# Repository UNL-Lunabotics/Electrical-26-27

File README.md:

# Electrical-26-27
Electrical's pcb projects and documentation.

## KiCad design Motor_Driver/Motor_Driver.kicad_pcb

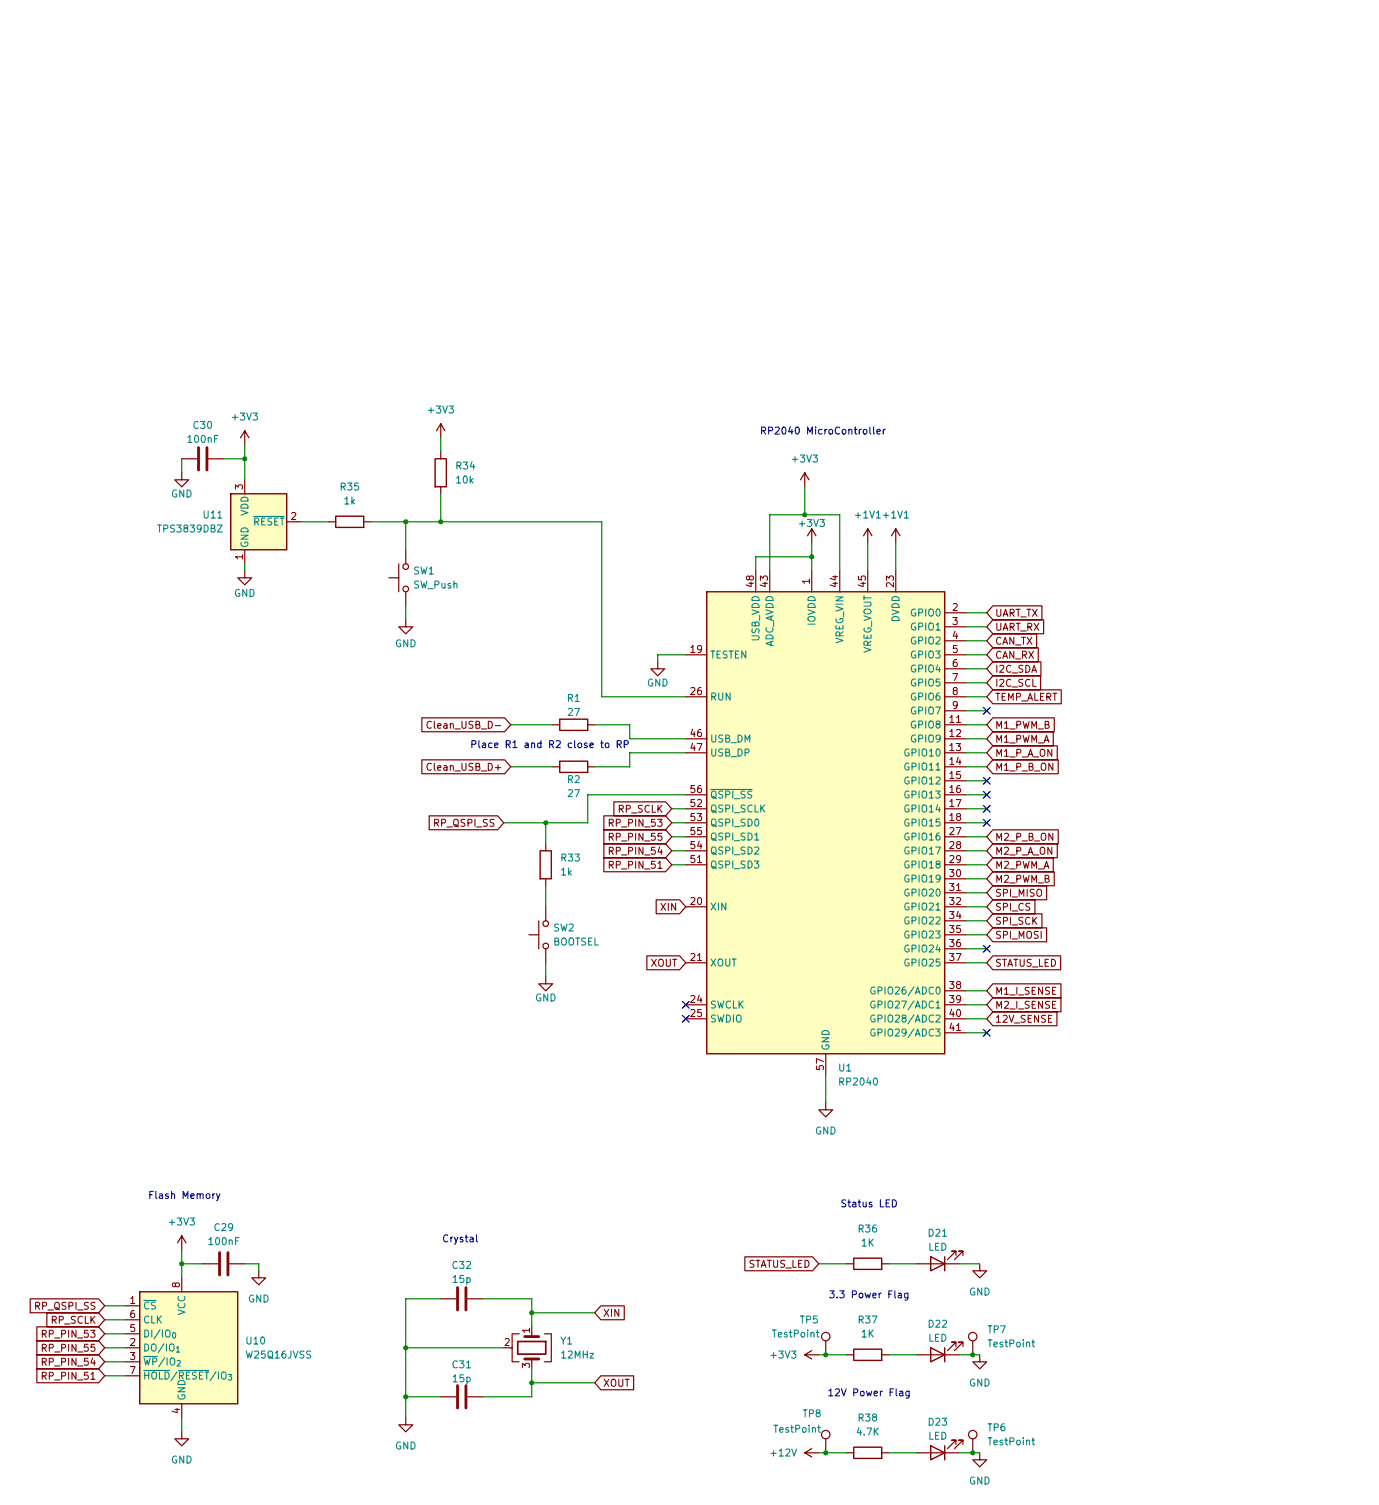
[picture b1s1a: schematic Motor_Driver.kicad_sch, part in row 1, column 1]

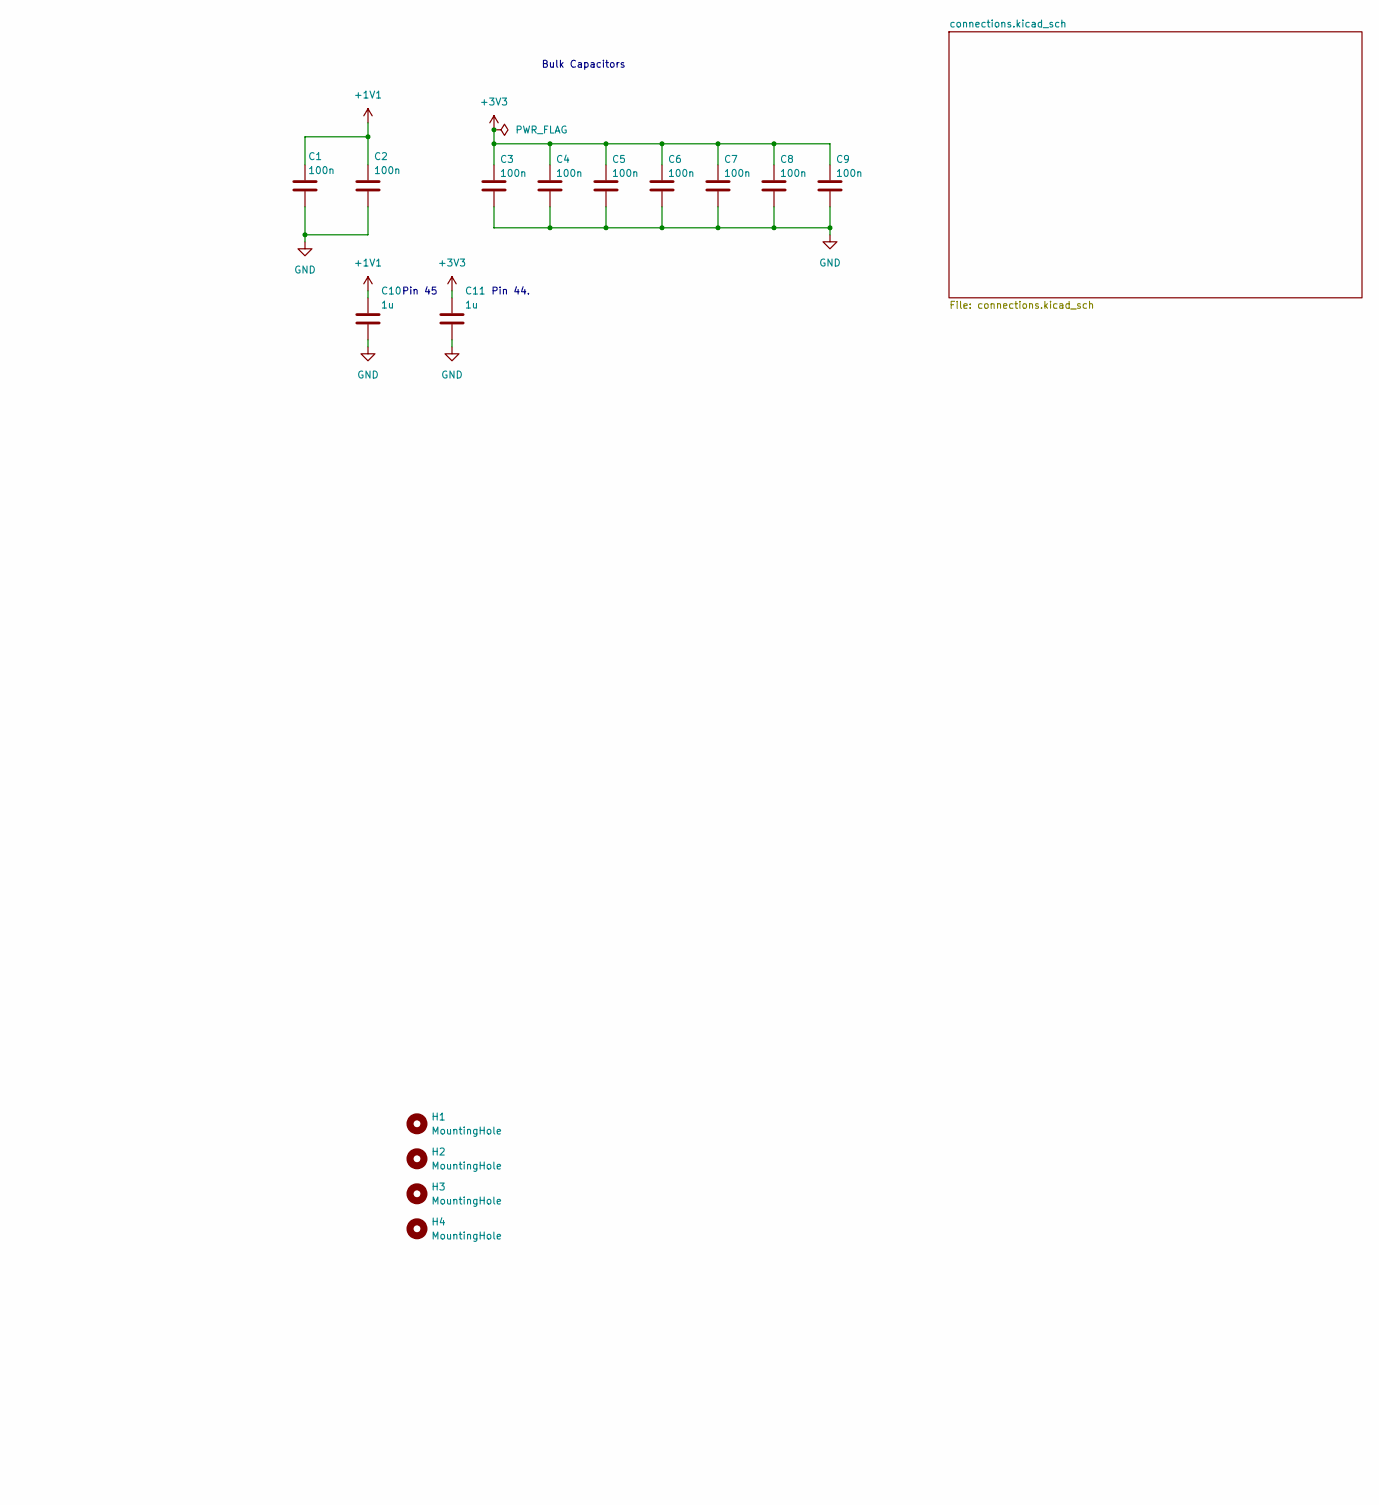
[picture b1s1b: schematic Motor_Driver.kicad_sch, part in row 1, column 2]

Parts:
C1, C2, C3, C4, C5, C6, C7, C8, C9: 100n; C_0805_2012Metric
C10, C11: 1u; C_0805_2012Metric
C29, C30: 100nF; C_0805_2012Metric
C31, C32: 15p; C_0805_2012Metric
D21, D22, D23: LED; LED_0805_2012Metric
H1, H2, H3, H4: MountingHole; MountingHole_3.2mm_M3
R1, R2: 27; R_0805_2012Metric
R33, R35: 1k; R_0805_2012Metric
R34: 10k; R_0805_2012Metric
R36, R37: 1K; R_0805_2012Metric
R38: 4.7K; R_0805_2012Metric
SW1: SW_Push; SW_PUSH_6mm
SW2: BOOTSEL; SW_PUSH_6mm
TP5, TP6, TP7, TP8: TestPoint; TestPoint_Pad_D1.5mm
U1: RP2040; QFN-56-1EP_7x7mm_P0.4mm_EP3.2x3.2mm
U10: W25Q16JVSS; SOIC-8_5.3x5.3mm_P1.27mm
U11: TPS3839DBZ; SOT-23
Y1: 12MHz; Crystal_SMD_3225-4Pin_3.2x2.5mm

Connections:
12V_SENSE: U1.40 (GPIO28/ADC2); also elsewhere on the board
+1V1: C1.1, C2.1, C10.1, U1.23 (DVDD), U1.45 (VREG_VOUT), U1.50 (DVDD)
+3V3: C3.1, C4.1, C5.1, C6.1, C7.1, C8.1, C9.1, C11.1, C29.1, C30.1, R34.1, R37.1, TP5.1 (1_1), U1.1 (IOVDD), U1.10 (IOVDD), U1.22 (IOVDD), U1.33 (IOVDD), U1.42 (IOVDD), U1.43 (ADC_AVDD), U1.44 (VREG_VIN), U1.48 (USB_VDD), U1.49 (IOVDD), U10.8 (VCC), U11.3 (VDD); also elsewhere on the board
+12V: R38.1, TP8.1 (1_1); also elsewhere on the board
CAN_RX: U1.5 (GPIO3); also elsewhere on the board
CAN_TX: U1.4 (GPIO2); also elsewhere on the board
Clean_USB_D+: R2.1; also elsewhere on the board
Clean_USB_D-: R1.1; also elsewhere on the board
GND: C1.2, C2.2, C3.2, C4.2, C5.2, C6.2, C7.2, C8.2, C9.2, C10.2, C11.2, C29.2, C30.2, C31.1, C32.1, D21.1 (K), D22.1 (K), D23.1 (K), SW1.1, SW2.1, TP6.1 (1_1), TP7.1 (1_1), U1.19 (TESTEN), U1.57 (GND), U10.4 (GND), U11.1 (GND), Y1.2 (G), Y1.4 (G); also elsewhere on the board
I2C_SCL: U1.7 (GPIO5); also elsewhere on the board
I2C_SDA: U1.6 (GPIO4); also elsewhere on the board
M1_I_SENSE: U1.38 (GPIO26/ADC0); also elsewhere on the board
M1_PWM_A: U1.12 (GPIO9); also elsewhere on the board
M1_PWM_B: U1.11 (GPIO8); also elsewhere on the board
M1_P_A_ON: U1.13 (GPIO10); also elsewhere on the board
M1_P_B_ON: U1.14 (GPIO11); also elsewhere on the board
M2_I_SENSE: U1.39 (GPIO27/ADC1); also elsewhere on the board
M2_PWM_A: U1.29 (GPIO18); also elsewhere on the board
M2_PWM_B: U1.30 (GPIO19); also elsewhere on the board
M2_P_A_ON: U1.28 (GPIO17); also elsewhere on the board
M2_P_B_ON: U1.27 (GPIO16); also elsewhere on the board
unnamed: D21.2 (A), R36.2
unnamed: D22.2 (A), R37.2
unnamed: D23.2 (A), R38.2
unnamed: R33.2, SW2.2
unnamed: R34.2, R35.2, SW1.2, U1.26 (RUN)
unnamed: R1.2, U1.46 (USB_DM)
unnamed: R2.2, U1.47 (USB_DP)
unnamed: R35.1, U11.2 (~RESET)
RP_PIN_51: U1.51 (QSPI_SD3), U10.7 (~HOLD/~RESET/IO_{3})
RP_PIN_53: U1.53 (QSPI_SD0), U10.5 (DI/IO_{0})
RP_PIN_54: U1.54 (QSPI_SD2), U10.3 (~WP/IO_{2})
RP_PIN_55: U1.55 (QSPI_SD1), U10.2 (DO/IO_{1})
RP_QSPI_SS: R33.1, U1.56 (~QSPI_SS), U10.1 (~CS)
RP_SCLK: U1.52 (QSPI_SCLK), U10.6 (CLK)
SPI_CS: U1.32 (GPIO21); also elsewhere on the board
SPI_MISO: U1.31 (GPIO20); also elsewhere on the board
SPI_MOSI: U1.35 (GPIO23); also elsewhere on the board
SPI_SCK: U1.34 (GPIO22); also elsewhere on the board
STATUS_LED: R36.1, U1.37 (GPIO25)
TEMP_ALERT: U1.8 (GPIO6); also elsewhere on the board
UART_RX: U1.3 (GPIO1); also elsewhere on the board
UART_TX: U1.2 (GPIO0); also elsewhere on the board
XIN: C32.2, U1.20 (XIN), Y1.1
XOUT: C31.2, U1.21 (XOUT), Y1.3

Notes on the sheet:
Pin 44.
12V Power Flag
Pin 45
Bulk Capacitors
Status LED
3.3 Power Flag
Flash Memory
Crystal
RP2040 MicroController
Place R1 and R2 close to RP

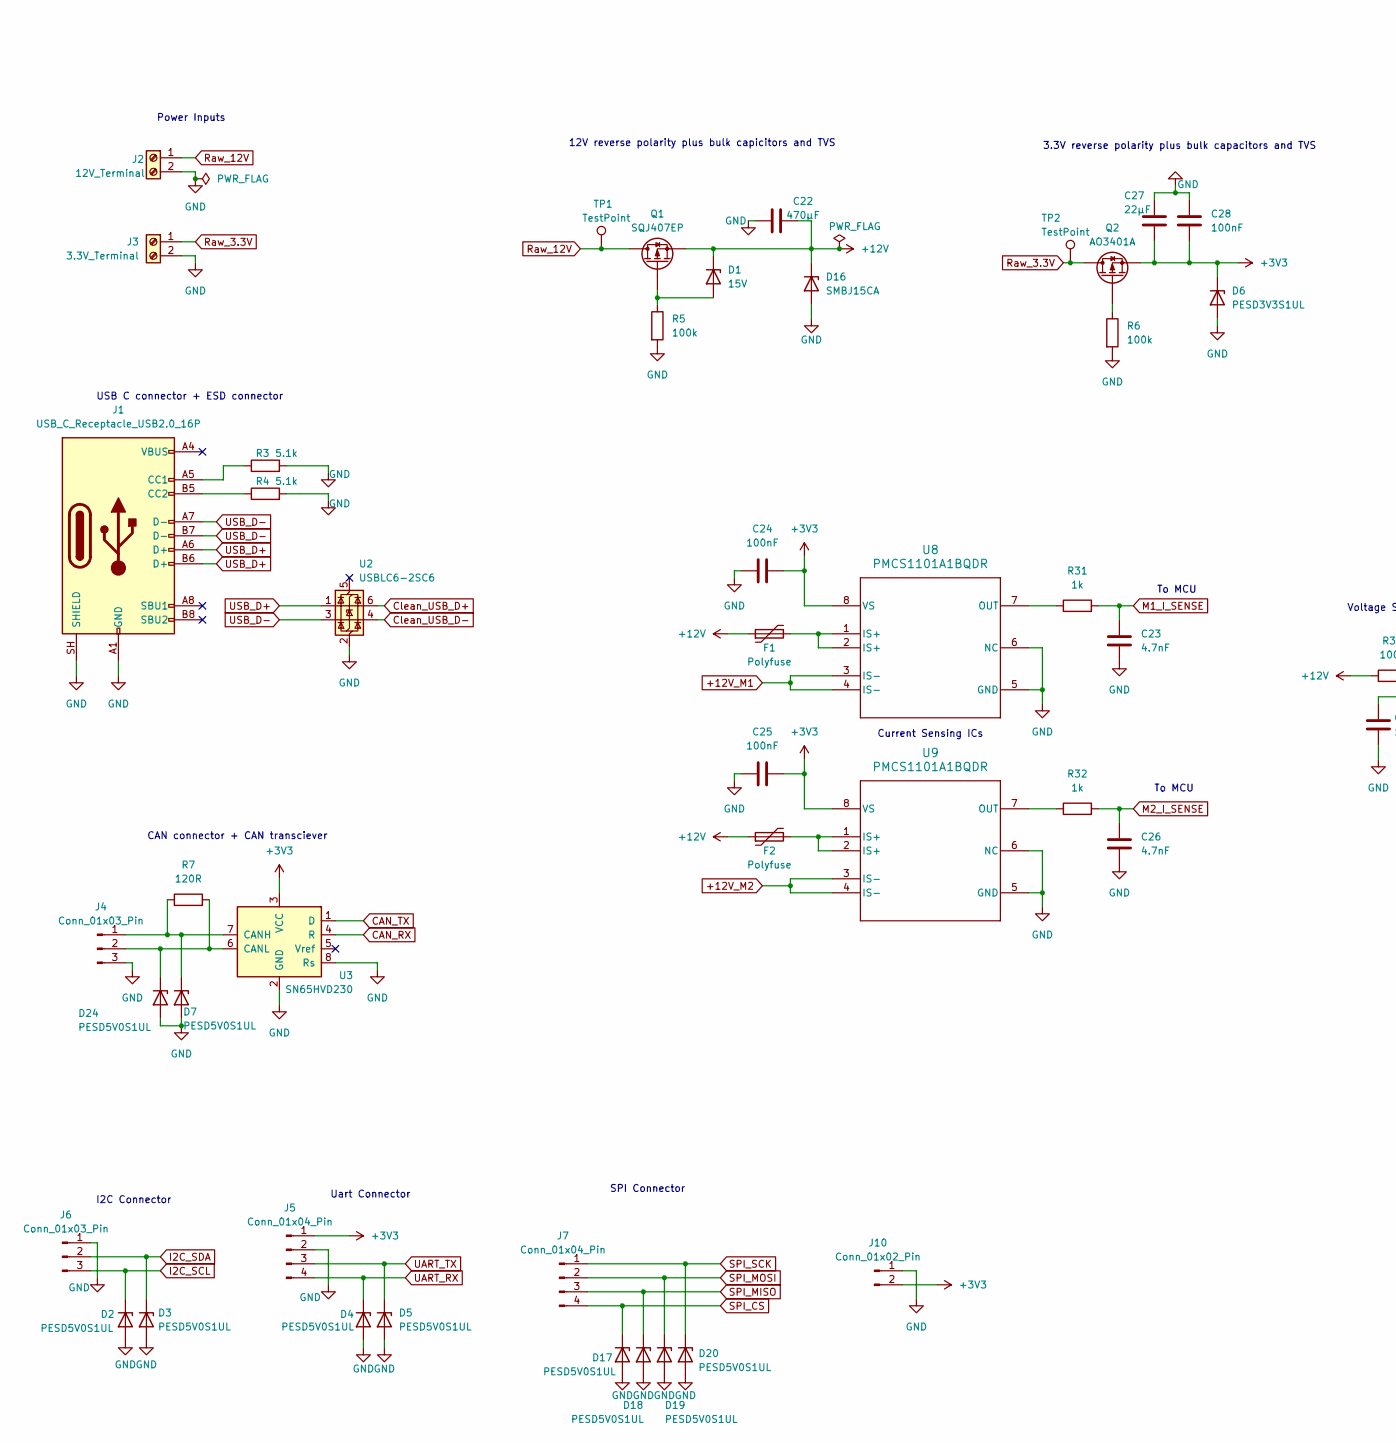
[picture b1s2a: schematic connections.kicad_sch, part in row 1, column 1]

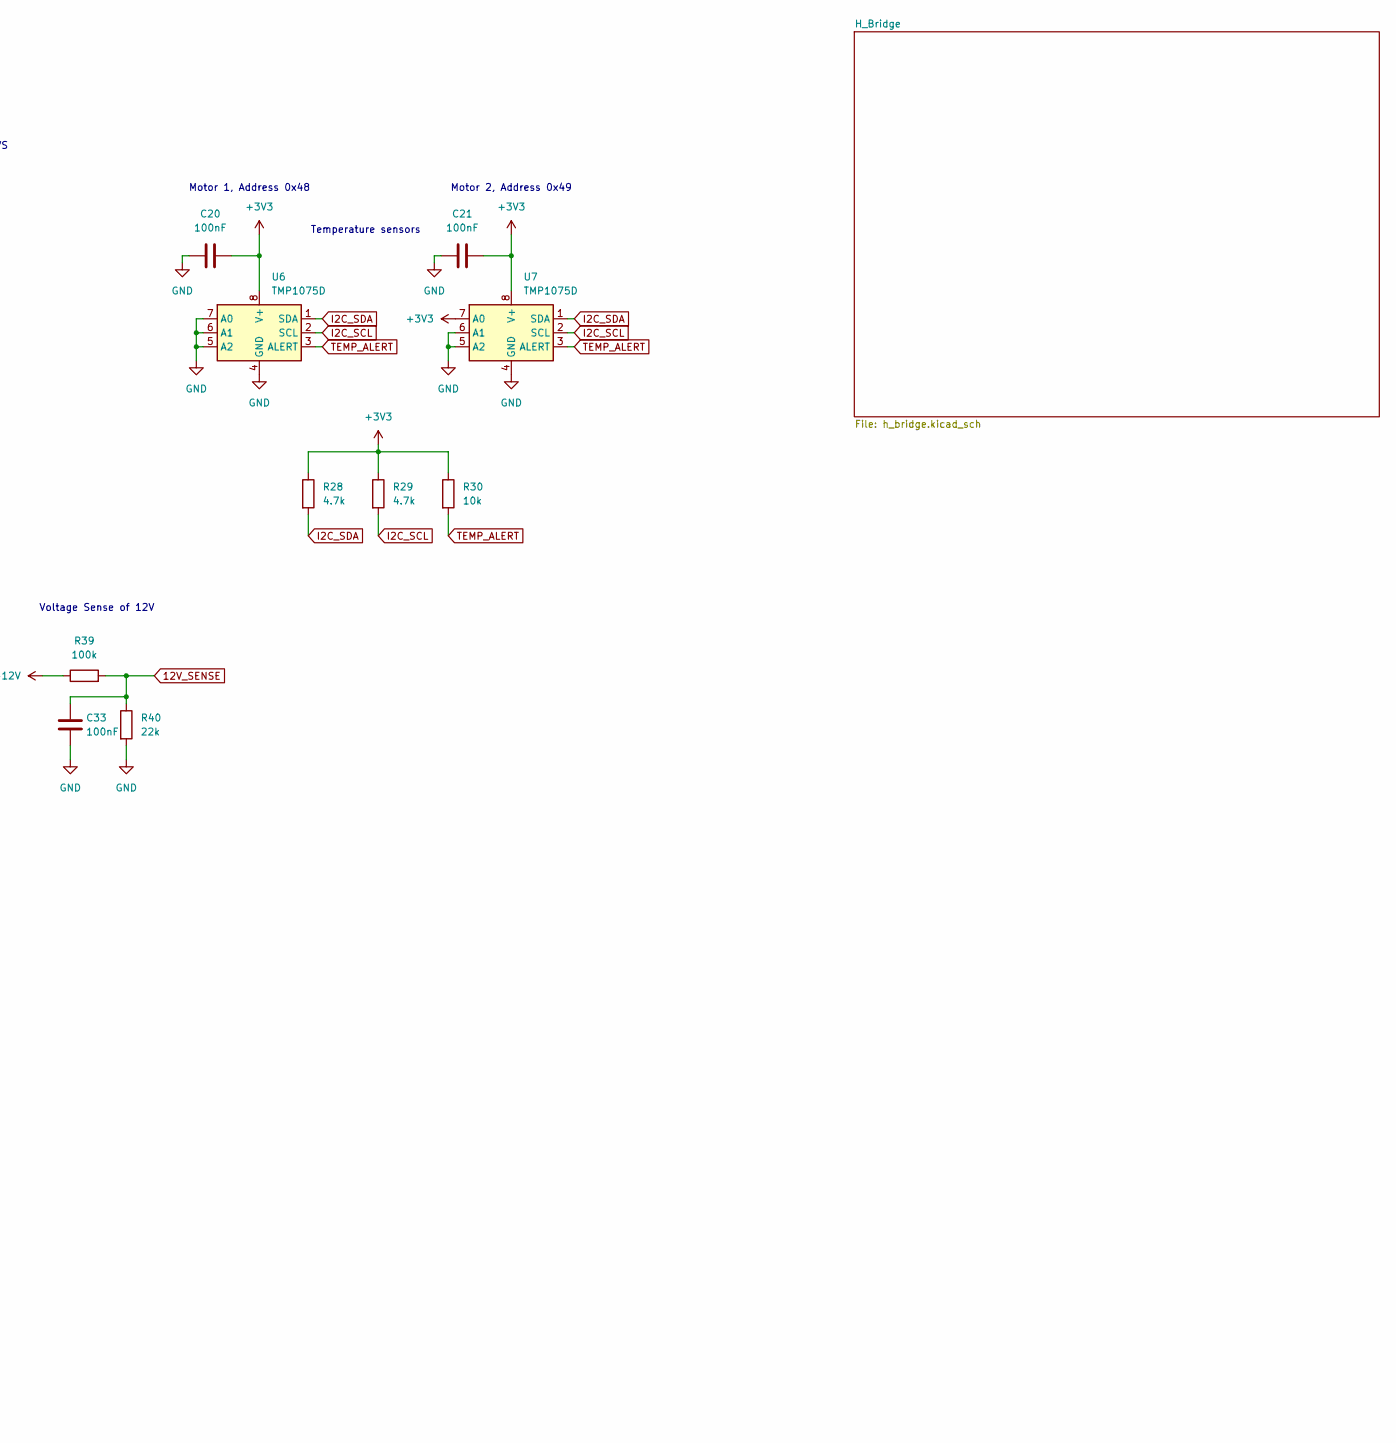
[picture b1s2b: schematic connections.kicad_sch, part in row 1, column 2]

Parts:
C20, C21, C24, C25, C28, C33: 100nF; C_0805_2012Metric
C22: 470μF; CP_Elec_10x10.5
C23, C26: 4.7nF; C_0805_2012Metric
C27: 22μF; C_0805_2012Metric
D1: 15V; D_SOD-123
D2, D3, D4, D5, D7, D17, D18, D19, D20, D24: PESD5V0S1UL; D_SOD-882
D6: PESD3V3S1UL; D_SOD-882
D16: SMBJ15CA; D_SMB
F1, F2: Polyfuse; Fuse_Mount
J1: USB_C_Receptacle_USB2.0_16P; USB_C_Receptacle_GCT_USB4105-xx-A_16P_TopMnt_Horizontal
J2: 12V_Terminal; TerminalBlock_MaiXu_MX126-5.0-02P_1x02_P5.00mm
J3: 3.3V_Terminal; TerminalBlock_MaiXu_MX126-5.0-02P_1x02_P5.00mm
J4, J6: Conn_01x03_Pin; JST_XH_B3B-XH-A_1x03_P2.50mm_Vertical
J5, J7: Conn_01x04_Pin; JST_XH_B4B-XH-A_1x04_P2.50mm_Vertical
J10: Conn_01x02_Pin; JST_XH_B2B-XH-A_1x02_P2.50mm_Vertical
Q1: SQJ407EP; PowerPAK_SO-8_Single_SGD
Q2: AO3401A; SOT-23_GSD
R3, R4: 5.1k; R_0805_2012Metric
R5, R6, R39: 100k; R_0805_2012Metric
R7: 120R; R_0805_2012Metric
R28, R29: 4.7k; R_0805_2012Metric
R30: 10k; R_0805_2012Metric
R31, R32: 1k; R_0805_2012Metric
R40: 22k; R_0805_2012Metric
TP1, TP2: TestPoint; TestPoint_Pad_D1.5mm
U2: USBLC6-2SC6; SOT-23-6
U3: SN65HVD230; SOIC-8_3.9x4.9mm_P1.27mm
U6, U7: TMP1075D; SO-8_3.9x4.9mm_P1.27mm
U8, U9: PMCS1101A1BQDR; D0008A_N

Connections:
12V_SENSE: C33.1, R39.2, R40.1; also elsewhere on the board
+3V3: C20.2, C21.2, C24.2, C25.2, C27.2, C28.2, D6.1 (K), J5.1, J10.2, Q2.S, R28.1, R29.1, R30.1, U3.3 (VCC), U6.8 (V+), U7.7 (A0), U7.8 (V+), U8.8 (VS), U9.8 (VS); also elsewhere on the board
+12V: C22.2, D1.1 (K), D16.1 (K), F1.1, F2.1, Q1.S, R39.1; also elsewhere on the board
+12V_M1: U8.3 (IS-), U8.4 (IS-); also elsewhere on the board
+12V_M2: U9.3 (IS-), U9.4 (IS-); also elsewhere on the board
CAN_RX: U3.4 (R); also elsewhere on the board
CAN_TX: U3.1 (D); also elsewhere on the board
Clean_USB_D+: U2.6 (I/O1); also elsewhere on the board
Clean_USB_D-: U2.4 (I/O2); also elsewhere on the board
GND: C20.1, C21.1, C22.1, C23.2, C24.1, C25.1, C26.2, C27.1, C28.1, C33.2, D2.2 (A), D3.2 (A), D4.2 (A), D5.2 (A), D6.2 (A), D7.2 (A), D16.2 (A), D17.2 (A), D18.2 (A), D19.2 (A), D20.2 (A), D24.2 (A), J1.A1 (GND), J1.A12 (GND), J1.B1 (GND), J1.B12 (GND), J1.SH (SHIELD), J2.2, J3.2, J4.3, J5.2, J6.1, J10.1, R3.2, R4.2, R5.2, R6.2, R40.2, U2.2 (GND), U3.2 (GND), U3.8 (Rs), U6.4 (GND), U6.5 (A2), U6.6 (A1), U6.7 (A0), U7.4 (GND), U7.5 (A2), U7.6 (A1), U8.5 (GND), U8.6 (NC), U9.5 (GND), U9.6 (NC); also elsewhere on the board
I2C_SCL: D2.1 (K), J6.3, R29.2, U6.2 (SCL), U7.2 (SCL); also elsewhere on the board
I2C_SDA: D3.1 (K), J6.2, R28.2, U6.1 (SDA), U7.1 (SDA); also elsewhere on the board
M1_I_SENSE: C23.1, R31.2; also elsewhere on the board
M2_I_SENSE: C26.1, R32.2; also elsewhere on the board
unnamed: D1.2 (A), Q1.G, R5.1
unnamed: D7.1 (K), J4.1, R7.1, U3.7 (CANH)
unnamed: D24.1 (K), J4.2, R7.2, U3.6 (CANL)
unnamed: F1.2, U8.1 (IS+), U8.2 (IS+)
unnamed: F2.2, U9.1 (IS+), U9.2 (IS+)
unnamed: J1.A5 (CC1), R3.1
unnamed: J1.B5 (CC2), R4.1
unnamed: Q2.G, R6.1
unnamed: R31.1, U8.7 (OUT)
unnamed: R32.1, U9.7 (OUT)
Raw_3.3V: J3.1, Q2.D, TP2.1 (1_1)
Raw_12V: J2.1, Q1.D, TP1.1 (1_1)
SPI_CS: D17.1 (K), J7.4; also elsewhere on the board
SPI_MISO: D18.1 (K), J7.3; also elsewhere on the board
SPI_MOSI: D19.1 (K), J7.2; also elsewhere on the board
SPI_SCK: D20.1 (K), J7.1; also elsewhere on the board
TEMP_ALERT: R30.2, U6.3 (ALERT), U7.3 (ALERT); also elsewhere on the board
UART_RX: D4.1 (K), J5.4; also elsewhere on the board
UART_TX: D5.1 (K), J5.3; also elsewhere on the board
USB_D+: J1.A6 (D+), J1.B6 (D+), U2.1 (I/O1)
USB_D-: J1.A7 (D-), J1.B7 (D-), U2.3 (I/O2)

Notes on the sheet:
Temperature sensors
Motor 1, Address 0x48
I2C Connector
To MCU
USB C connector + ESD connector
3.3V reverse polarity plus bulk capacitors and TVS
12V reverse polarity plus bulk capicitors and TVS
Current Sensing ICs
Motor 2, Address 0x49
CAN connector + CAN transciever
Power Inputs
Voltage Sense of 12V
SPI Connector
Uart Connector

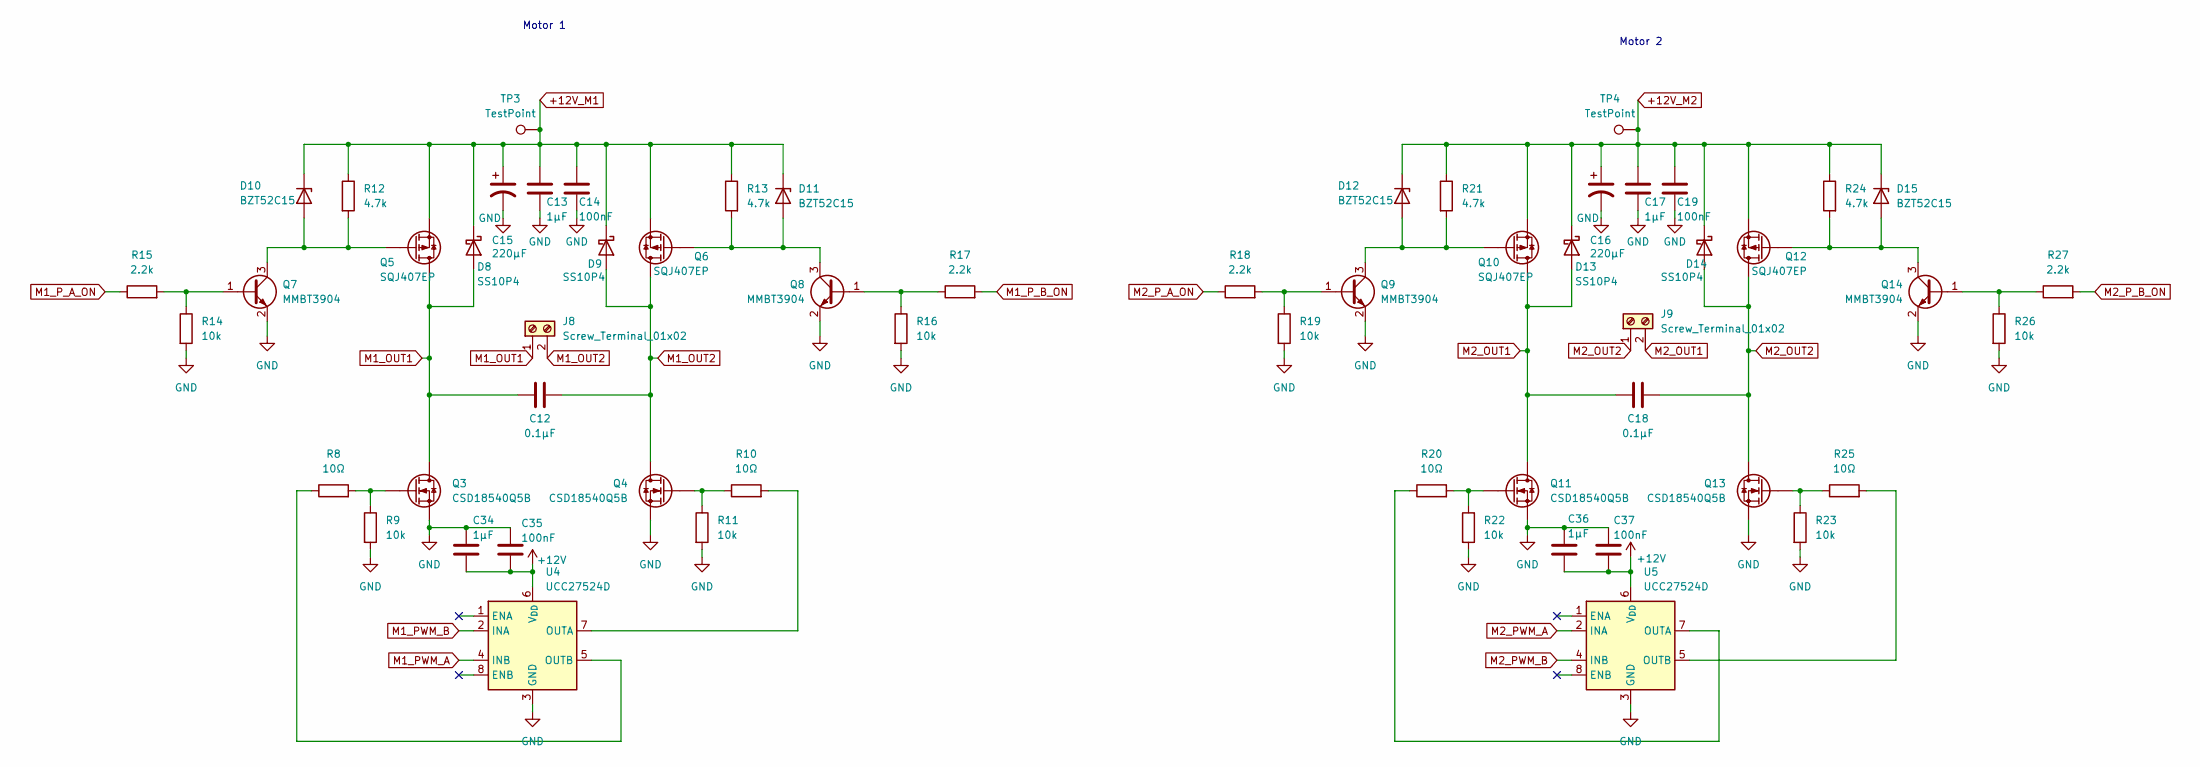
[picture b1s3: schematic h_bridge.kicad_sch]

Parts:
C12, C18: 0.1μF; C_0805_2012Metric
C13, C17, C34, C36: 1μF; C_0805_2012Metric
C14, C19, C35, C37: 100nF; C_0805_2012Metric
C15, C16: 220μF; CP_Elec_8x10.5
D8, D9, D13, D14: SS10P4; TO-277A_SS10P4_K-tab
D10, D11, D12, D15: BZT52C15; D_SOD-123
J8, J9: Screw_Terminal_01x02; TerminalBlock_MaiXu_MX126-5.0-02P_1x02_P5.00mm
Q3, Q4, Q11, Q13: CSD18540Q5B; TDSON-8-1_SGD
Q5, Q6, Q10, Q12: SQJ407EP; PowerPAK_SO-8_Single_SGD
Q7, Q8, Q9, Q14: MMBT3904; SOT-23
R8, R10, R20, R25: 10Ω; R_0805_2012Metric
R9, R11, R14, R16, R19, R22, R23, R26: 10k; R_0805_2012Metric
R12, R13, R21, R24: 4.7k; R_0805_2012Metric
R15, R17, R18, R27: 2.2k; R_0805_2012Metric
TP3, TP4: TestPoint; TestPoint_Pad_D1.5mm
U4, U5: UCC27524D; SOIC-8_3.9x4.9mm_P1.27mm

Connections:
+12V: C34.2, C35.2, C36.2, C37.2, U4.6 (V_{DD}), U5.6 (V_{DD}); also elsewhere on the board
+12V_M1: C13.1, C14.1, C15.1, D8.1 (K), D9.1 (K), D10.1 (K), D11.1 (K), Q5.S, Q6.S, R12.1, R13.1, TP3.1 (1_1); also elsewhere on the board
+12V_M2: C16.1, C17.1, C19.1, D12.1 (K), D13.1 (K), D14.1 (K), D15.1 (K), Q10.S, Q12.S, R21.1, R24.1, TP4.1 (1_1); also elsewhere on the board
GND: C13.2, C14.2, C15.2, C16.2, C17.2, C19.2, C34.1, C35.1, C36.1, C37.1, Q3.S, Q4.S, Q7.2 (E), Q8.2 (E), Q9.2 (E), Q11.S, Q13.S, Q14.2 (E), R9.2, R11.2, R14.2, R16.2, R19.2, R22.2, R23.2, R26.2, U4.3 (GND), U5.3 (GND); also elsewhere on the board
M1_OUT1: C12.1, D8.2 (A), J8.1, Q3.D, Q5.D
M1_OUT2: C12.2, D9.2 (A), J8.2, Q4.D, Q6.D
M1_PWM_A: U4.4 (INB); also elsewhere on the board
M1_PWM_B: U4.2 (INA); also elsewhere on the board
M1_P_A_ON: R15.1; also elsewhere on the board
M1_P_B_ON: R17.2; also elsewhere on the board
M2_OUT1: C18.1, D13.2 (A), J9.2, Q10.D, Q11.D
M2_OUT2: C18.2, D14.2 (A), J9.1, Q12.D, Q13.D
M2_PWM_A: U5.2 (INA); also elsewhere on the board
M2_PWM_B: U5.4 (INB); also elsewhere on the board
M2_P_A_ON: R18.1; also elsewhere on the board
M2_P_B_ON: R27.2; also elsewhere on the board
unnamed: D10.2 (A), Q5.G, Q7.3 (C), R12.2
unnamed: D11.2 (A), Q6.G, Q8.3 (C), R13.2
unnamed: D12.2 (A), Q9.3 (C), Q10.G, R21.2
unnamed: D15.2 (A), Q12.G, Q14.3 (C), R24.2
unnamed: Q3.G, R8.2, R9.1
unnamed: Q4.G, R10.1, R11.1
unnamed: Q7.1 (B), R14.1, R15.2
unnamed: Q8.1 (B), R16.1, R17.1
unnamed: Q9.1 (B), R18.2, R19.1
unnamed: Q11.G, R20.2, R22.1
unnamed: Q13.G, R23.1, R25.1
unnamed: Q14.1 (B), R26.1, R27.1
unnamed: R10.2, U4.7 (OUTA)
unnamed: R8.1, U4.5 (OUTB)
unnamed: R20.1, U5.7 (OUTA)
unnamed: R25.2, U5.5 (OUTB)

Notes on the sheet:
Motor 1
Motor 2

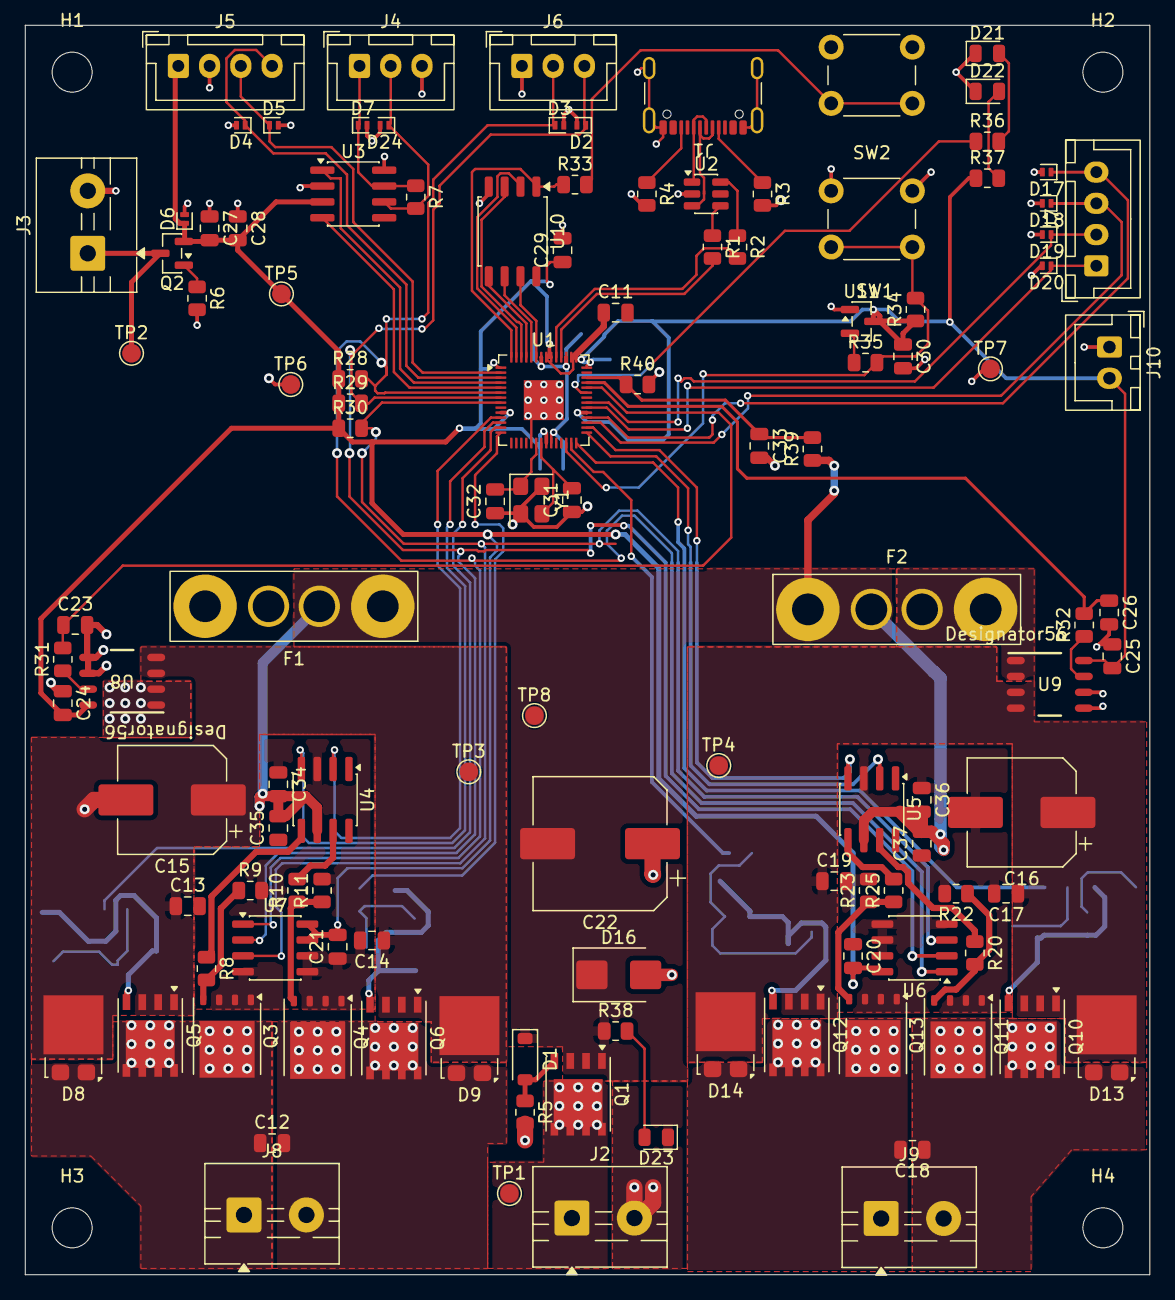
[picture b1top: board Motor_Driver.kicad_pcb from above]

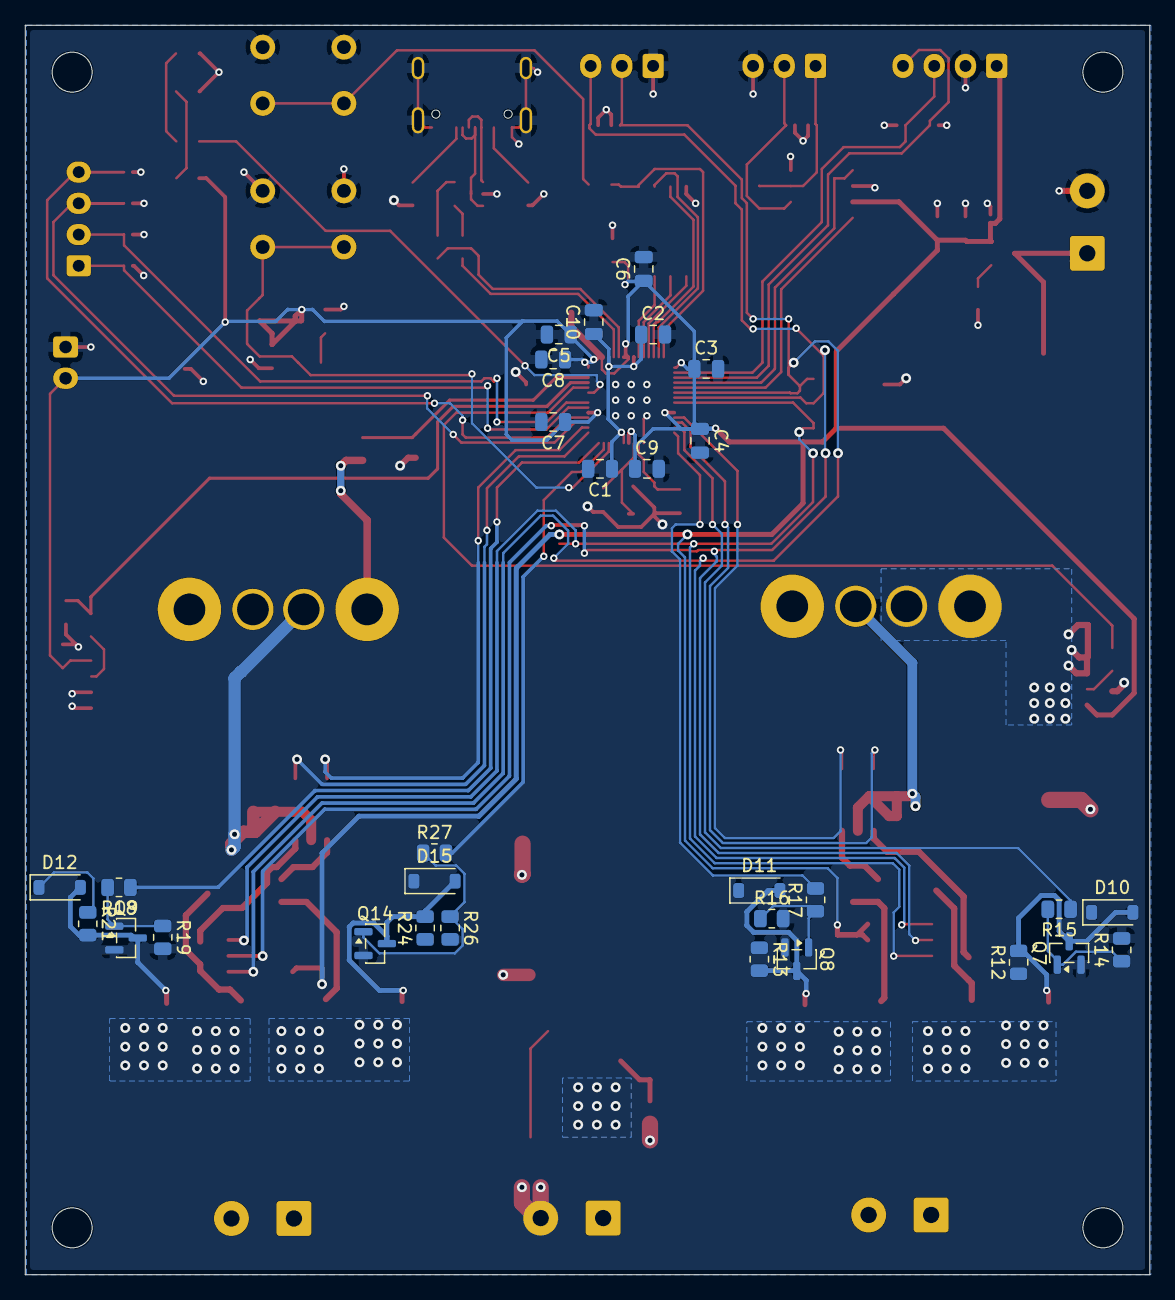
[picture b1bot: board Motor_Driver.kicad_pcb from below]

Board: 2 copper layers, 90.0 x 100.0 mm, 153 parts (30 on the bottom side), 81 nets.
